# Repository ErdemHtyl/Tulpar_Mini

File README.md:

# MiniTULPAR — Custom Flight Controller Board (FCB)

> A quadcopter flight controller designed from scratch around the STM32F405.
> Schematic, 4-layer PCB, power architecture, sensor integration and firmware
> all live in this repository — no existing open-source flight controller is
> used.

---

## ⚠️ Project Status

This project is **under active development**. The table below shows what is
finished and what is still in progress:

| Component | Status | Notes |
|---|---|---|
| Schematic design | ✅ Rev A complete | `MiniTulpar_Schematic.pdf` |
| PCB layout (4 layer) | ✅ Complete | 53.6 × 53.6 mm, 1.6 mm |
| Manufacturing files (Gerber/BOM/CPL) | ✅ Generated | `mfr/` |
| System architecture documentation | ✅ Complete | `docs/architecture.md` |
| Pin configuration (CubeMX) | ✅ Verified | No timer channel conflicts |
| Clock tree configuration | ✅ Verified | 168 MHz SYSCLK, 48 MHz USB |
| Board fabrication and assembly | 🔄 Planned | — |
| **Firmware** | 🚧 **In development — not started** | See the roadmap below |
| Flight testing | ⏳ Blocked | Depends on firmware |
| Lower-cost board variants | 🔄 Planned | See [Planned Variants](#planned-variants) |

> **Firmware note:** the firmware is **in development**. Nothing described in
> the roadmap below has been implemented yet — drivers, sensor fusion, PID
> control and the safety layer are all still to be written. The architectural
> decisions behind them (bus allocation, timer/DMA assignments, interrupt
> priorities) are documented in advance in `docs/architecture.md`, and
> development will follow that document. **The board does not fly in its
> current state.**

---

## Table of Contents

- [Project Goal](#project-goal)
- [Hardware Overview](#hardware-overview)
- [System Architecture](#system-architecture)
- [Bus Allocation and Rationale](#bus-allocation-and-rationale)
- [Timer and DMA Allocation](#timer-and-dma-allocation)
- [Pin Map](#pin-map)
- [Clock Configuration](#clock-configuration)
- [Firmware Roadmap](#firmware-roadmap)
- [Planned Variants](#planned-variants)
- [Repository Layout](#repository-layout)
- [Development Environment](#development-environment)
- [Known Issues and Rev B Notes](#known-issues-and-rev-b-notes)
- [License](#license)

---

## Project Goal

The goal is to **design, understand and implement every hardware and software
component** rather than buying an off-the-shelf flight controller (Betaflight /
ArduPilot hardware). That includes:

- Multi-layer PCB design and power architecture
- Writing IMU / barometer / magnetometer drivers from scratch
- Sensor fusion (Mahony / Madgwick / EKF)
- PID-based stabilisation and mixing
- Generating the DShot ESC protocol directly from timers and DMA
- GPS, telemetry, blackbox logging and the failsafe/safety layer

Every design decision is recorded in `docs/architecture.md` together with the
alternative that was rejected and the reason it was rejected.

---

## Hardware Overview

| Feature | Value |
|---|---|
| MCU | **STM32F405RGT6** — Cortex-M4F, 168 MHz, 1 MB Flash, 192 KB RAM (128 KB SRAM + 64 KB CCM) |
| Oscillator | 8 MHz HSE (ECS-80-10-30B-CKM-TR) |
| PCB | 4 layer, 53.6 × 53.6 mm, 1.6 mm thickness |
| Power | USB-C 5 V ↔ VIN, Schottky OR (D2/D3) + JP1 jumper → **LD39200PU33R** 3.3 V / 2 A LDO |
| IMU | **ICM-42670-P** (accel + gyro) — SPI1 @ 21 MHz, INT1 → PC4 |
| Barometer | **BMP581** — I2C2, 0x46, INT → PB1 |
| Magnetometer | **IIS2MDC** — I2C2, 0x1E, DRDY → PB2 |
| Blackbox flash | **W25Q128JVS** 16 MB — SPI2 @ 21 MHz |
| Motor outputs | 4× **DShot600** — TIM8_CH1..CH4 (PC6–PC9), single DMA burst |
| Auxiliary PWM | TIM1_CH1/CH3 (PA8/PA10) + TIM3_CH1/CH2 (PB4/PB5 — camera gimbal) |
| RC input | CRSF / ELRS — UART4 (J10) |
| GPS | USART2 (J12) |
| Telemetry | UART5 (J11) |
| Spare UART | USART3 (J5) |
| External I²C | I2C1 (J6) — separate from the internal sensor bus |
| ADC | Battery voltage → PC3 (ADC1_IN13), external → PC2 (ADC1_IN12) |
| USB | USB-C 2.0, USBLC6-2SC6 ESD protection + polyfuse + 5.1 kΩ CC |
| Debug | 10-pin 1.27 mm SWD (J13) |
| LEDs | 3× status LEDs + power LED |

---

## System Architecture

```mermaid
flowchart TB
    subgraph PWR["Power Tree"]
        XT[["VIN / Rail"]]
        USB5[["USB-C 5 V"]]
        OR{{"D2 / D3 Schottky OR<br/>+ JP1"}}
        LDO["U1 LD39200PU33R<br/>3.3 V / 2 A"]
        XT --> OR
        USB5 --> OR
        OR --> LDO
        LDO --> V33[("+3.3 V")]
        LDO -. "FB1 600Ω@100MHz" .-> VDDA[("VDDA")]
    end

    subgraph MCU["STM32F405RGT6 @ 168 MHz"]
        CORE["Cortex-M4F<br/>FPU + DSP"]
    end

    subgraph FAST["High rate — SPI1 @ 21 MHz"]
        IMU["U2 ICM-42670-P<br/>CS = PA4 · INT1 → PC4"]
    end

    subgraph SLOW["Slow sensor bus — I2C2 @ 400 kHz"]
        BARO["U4 BMP581 · 0x46"]
        MAG["U6 IIS2MDC · 0x1E"]
    end

    subgraph LOG["Logging — SPI2 @ 21 MHz"]
        FLASH["U7 W25Q128JVS<br/>16 MB · CS = PB12"]
    end

    subgraph ACT["Actuators"]
        ESC["4× ESC · DShot600<br/>TIM8_CH1..CH4"]
        SERVO["Aux PWM · TIM1 / TIM3"]
    end

    subgraph COMM["Serial links"]
        RC["CRSF/RC · UART4"]
        GPS["GPS · USART2"]
        TLM["Telemetry · UART5"]
        AUX["Spare · USART3"]
        EXTI2C["External I2C1"]
    end

    V33 --> MCU
    IMU <-->|SPI1| CORE
    BARO <-->|I2C2| CORE
    MAG <-->|I2C2| CORE
    FLASH <-->|SPI2| CORE
    CORE --> ESC
    CORE --> SERVO
    RC <--> CORE
    GPS <--> CORE
    TLM <--> CORE
    AUX <--> CORE
    EXTI2C <--> CORE
```

**The critical data path:** the IMU's INT1 line raises an EXTI interrupt → a
SPI1 DMA burst read starts → the DMA completion interrupt runs the filter, PID
and mixer chain → the result is encoded into a DShot frame and handed to the
TIM8 DMA. The whole chain completes **inside one interrupt context**, never
waiting on any other peripheral.

---

## Bus Allocation and Rationale

The founding principle of the architecture:

> **The critical path lives on SPI. Everything non-critical lives on I²C.**

| Device | Bus | Speed | Why |
|---|---|---|---|
| ICM-42670-P | **SPI1** (alone) | 21 MHz | The only high-rate path; the same read takes ~68× longer on I²C |
| BMP581 + IIS2MDC | **I2C2** (shared) | 400 kHz | ~4 % combined bus load; neither is on the critical path |
| W25Q128JVS | **SPI2** (alone) | 21 MHz | A sector erase can take 400 ms and must never delay a gyro read |
| External devices | **I2C1** | 400 kHz | A cable means ESD, capacitance and lockup risk — isolated from the internal sensors |

**Why the IMU is on SPI.** A 15-byte sample read takes ~5.7 µs on SPI1 versus
~388 µs on I²C Fast-mode:

| Loop rate | SPI load | I²C load |
|---|---|---|
| 1 kHz | 0.6 % | 39 % |
| 1.6 kHz | 0.9 % | 62 % |
| 4 kHz | 2.3 % | impossible |

Beyond bandwidth: SPI is deterministic (no clock stretching), has no bus-lockup
failure mode, survives the noisy environment of ESCs switching at 20–40 kHz
thanks to its push-pull drivers, and costs the CPU nothing when paired with DMA.

---

## Timer and DMA Allocation

### Timer assignment

The current CubeMX pin configuration is **conflict-free** — all four motor
outputs, both auxiliary PWM channels and both gimbal channels are usable at the
same time:

| Function | Timer | Channel | Pin | Timer clock |
|---|---|---|---|---|
| Motor 1–4 | **TIM8** | CH1–CH4 | PC6 / PC7 / PC8 / PC9 | 168 MHz (APB2) |
| Aux PWM 1–2 | TIM1 | CH1 / CH3 | PA8 / PA10 | 168 MHz (APB2) |
| Camera gimbal 1–2 | TIM3 | CH2 / CH1 | PB5 / PB4 | 84 MHz (APB1) |

The motors are on **TIM8** rather than TIM3 for four reasons:

1. TIM3_CH1 can be routed to either PC6 or PB4, but only one at a time — putting
   the motors on TIM8 leaves TIM3 entirely free for the gimbal outputs.
2. TIM8 sits on APB2, so its timer clock is 168 MHz (twice TIM3's) — twice the
   DShot bit-timing resolution.
3. TIM8 is an advanced-control timer: its break input can drive a hardware motor
   cutoff for failsafe later.
4. All four motors on one timer are bit-synchronous and need only a single DMA
   burst (TIM8_UP + DMAR).

Because the two gimbal channels sit on TIM3 (84 MHz) and the aux PWM channels on
TIM1 (168 MHz), driving both at a common servo rate means programming the two
timers separately with different prescaler values.

### DShot600 timing (TIM8 @ 168 MHz)

| Protocol | ARR | CCR for "0" | CCR for "1" | Frame |
|---|---|---|---|---|
| DShot300 | 559 | 210 | 420 | 53.3 µs |
| **DShot600** | **279** | **105** | **210** | **26.7 µs** |

DShot is digital: **ESC calibration stops being a step that exists**, and every
frame carries a 4-bit CRC — a command corrupted by noise is discarded by the ESC
instead of silently applying the wrong throttle.

### DMA assignments (under the RM0090 Table 42/43 constraints)

**DMA2**

| Stream | Ch | Assignment |
|---|---|---|
| S0 | 3 | SPI1_RX — IMU read *(the critical path)* |
| S1 | 7 | TIM8_UP — DShot burst output |
| S5 | 3 | SPI1_TX — IMU command |
| S2/S3/S4/S7 | 7 | *Reserved:* bidirectional DShot (unused in v1) |

**DMA1**

| Stream | Ch | Assignment |
|---|---|---|
| S0 | 4 | UART5_RX — telemetry |
| S1 | 4 | USART3_RX — spare |
| S2 | 4 | UART4_RX — CRSF/RC *(420 kbaud, critical)* |
| S3 | 0 | SPI2_RX — flash |
| S4 | 0 | SPI2_TX — blackbox |
| S5 | 4 | USART2_RX — GPS (circular + IDLE) |
| S6 | 4 | USART2_TX — GPS configuration |
| S7 | 4 | UART5_TX — telemetry |

I2C1/I2C2, UART4_TX, USART3_TX and ADC1 are interrupt-driven — their streams
went to higher-value work and their load is negligible.

### Interrupt priorities (NVIC)

| Priority | Interrupt |
|---|---|
| 0 | EXTI4 — IMU INT1 (timestamps the sampling instant) |
| 1 | DMA2_S0 — SPI1_RX complete (triggers the control chain) |
| 2 | DMA2_S1 — TIM8_UP (motor frame) |
| 3 | DMA1_S2 — UART4_RX (RC / failsafe) |
| 4 | DMA1_S5 — USART2_RX (GPS) |
| 5 | I2C2_EV / I2C2_ER |
| 6 | SysTick |
| 7 | Flash, UART5, USB |

> **The rule:** blackbox writes, USB and telemetry must **never** preempt the
> control loop.

### Target timing budget (1 kHz loop)

| Step | Duration | Occupies the CPU? |
|---|---|---|
| IMU SPI burst read | 5.7 µs | No (DMA) |
| Filtering (3× biquad + PT1) | ~10 µs | Yes |
| Attitude update (Mahony) | ~20 µs | Yes |
| PID (3 axes) | ~12 µs | Yes |
| Mixer + motor limiting | ~4 µs | Yes |
| DShot frame encoding | ~6 µs | Yes |
| **Total CPU** | **~52 µs** | **≈ 5 % load** |

---

## Pin Map

This table is the single source of truth for the pin map — it is never
maintained in two places.

| Port | Signal | Function |
|---|---|---|
| PA4 / PA5 / PA6 / PA7 | SPI1 CS/SCK/MISO/MOSI | IMU |
| PC4 | INT_IMU1 | EXTI4 — data ready |
| PB12 / PB13 / PB14 / PB15 | SPI2 CS/SCK/MISO/MOSI | Blackbox flash |
| PB10 / PB11 | I2C2 SCL/SDA | Internal sensor bus |
| PB1 / PB2 | INT_BAR / INT_MAG | EXTI1 / EXTI2 |
| PB8 / PB9 | I2C1 SCL/SDA | External connector (J6) |
| PC6 / PC7 / PC8 / PC9 | DSHOT_1..4 | **TIM8_CH1..CH4** |
| PA8 / PA10 | Aux PWM 1–2 | TIM1_CH1 / TIM1_CH3 |
| PB4 / PB5 | CAM_GIMBAL2 / CAM_GIMBAL1 | TIM3_CH1 / TIM3_CH2 |
| PA0 / PA1 | UART4 TX/RX | CRSF / RC (J10) |
| PA2 / PA3 | USART2 TX/RX | GPS (J12) |
| PC12 / PD2 | UART5 TX/RX | Telemetry (J11) |
| PC10 / PC11 | USART3 TX/RX | Spare (J5) |
| PC2 / PC3 | ADC1_IN12 / ADC1_IN13 | External ADC / battery |
| PA11 / PA12 / PA9 | USB DM/DP/VBUS | USB-C |
| PA13 / PA14 | SWDIO / SWCLK | SWD (J13) |
| PC13 / PC14 / PC15 | LD1 / LD2 / LD3 | Status LEDs |
| PH0 / PH1 | HSE IN/OUT | 8 MHz crystal |

**Unused and available:** PA15, PB0, PB3, PB6, PB7, PC0, PC1, PC5.
PB6/PB7 = USART1, PB0/PB1 = TIM3_CH3/CH4, and PB0 + PC5 together are exactly the
chip select + interrupt pair a second IMU would need.

Full pin table including physical pin numbers: [`docs/architecture.md`](docs/architecture.md)

---

## Clock Configuration

8 MHz HSE crystal → PLL (M = 4, N = 168, P = 2) → **168 MHz SYSCLK**, with the
PLL Q divider set to 7 for the 48 MHz USB clock. CSS (clock security system) is
enabled, so a crystal failure falls back to the HSI instead of stopping the
core.

| Domain | Prescaler | Frequency |
|---|---|---|
| SYSCLK / HCLK (AHB, core, memory, DMA) | /1 | **168 MHz** |
| APB1 peripheral clock (PCLK1) | /4 | 42 MHz |
| APB1 timer clock (TIM3 …) | — | 84 MHz |
| APB2 peripheral clock (PCLK2) | /2 | 84 MHz |
| APB2 timer clock (**TIM1, TIM8**) | — | **168 MHz** |
| USB OTG FS | PLL /Q = 7 | 48 MHz |
| IWDG | LSI | 32 kHz |

The RTC runs from the internal LSI — no LSE crystal is fitted, because PC14/PC15
are used as status LED outputs. This is irrelevant for a flight controller.

SPI1 and SPI2 both run at 21 MHz: SPI1 from PCLK2 (84 MHz ÷ 4) and SPI2 from
PCLK1 (42 MHz ÷ 2), both comfortably under the ICM-42670-P's 24 MHz and the
W25Q128's 133 MHz limits.

---

## Firmware Roadmap

> 🚧 **Nothing in this section has been implemented yet.** The order is chosen to
> minimise bring-up risk; each step depends on the previous one being verified.

### Stage 0 — Bring-up
- [ ] Project skeleton and build system
- [ ] SWD connection and LED blink — is the board alive?
- [ ] Bring up the clock tree on hardware and measure it (8 MHz HSE → 168 MHz)
- [ ] Generate the pin configuration from the pin map above
- [ ] Debug console over USB CDC

### Stage 1 — Sensors
- [ ] SPI1 + DMA driver, ICM-42670-P WHO_AM_I
- [ ] Raw IMU reads (INT1 → EXTI → DMA burst chain)
- [ ] IMU internal UI filter / ODR configuration *(anti-aliasing is critical)*
- [ ] I2C2 as a **non-blocking state machine** + timeouts + bus recovery (9× SCL)
- [ ] BMP581 driver (pressure → altitude)
- [ ] IIS2MDC driver + hard/soft-iron calibration
- [ ] Gyro/accel calibration and temperature compensation

### Stage 2 — Actuators
- [ ] DShot600 frame generation via TIM8 + DMAR burst
- [ ] Motor test mode — **props off**, verify frames on a scope
- [ ] Mixer (quad X), motor limiting / airmode

### Stage 3 — Control
- [ ] Gyro filter chain (biquad LPF + notch + PT1)
- [ ] Attitude estimation — Mahony (EKF later)
- [ ] Rate PID loop (acro mode)
- [ ] Angle/horizon loop (self-level)
- [ ] PID gain tuning interface

### Stage 4 — RC and safety
- [ ] CRSF parser (UART4 DMA + IDLE line)
- [ ] Arming/disarming state machine + sensor health check
- [ ] **IWDG** (~50 ms, fed only by the main control loop)
- [ ] Gyro timeout → immediate disarm
- [ ] RC timeout (~500 ms) → progressive throttle-cut failsafe
- [ ] Battery voltage monitoring + low-voltage warning

### Stage 5 — Navigation and logging
- [ ] GPS UBX/NMEA parser (USART2 DMA)
- [ ] Blackbox logging (SPI2 → W25Q128, pre-erase while idle)
- [ ] Telemetry (UART5) and the CRSF back-channel
- [ ] Altitude hold → position hold → return-to-home

### Stage 6 — Advanced
- [ ] Bidirectional DShot (RPM telemetry) + RPM-based notch filtering
- [ ] EKF-based sensor fusion
- [ ] Host-side unit tests (HIL/SIL)

**The safety layer is non-negotiable:** motors are **always** disarmed at
power-up; arming requires low throttle plus an explicit arm command plus a
sensor health check.

---

## Planned Variants

MiniTULPAR Rev A is the reference design — it is deliberately built with
good parts rather than cheap ones, so that when something misbehaves the cause
is the design and not the bill of materials.

**More affordable versions of this board will be added later.** The plan is to
publish lower-cost variants alongside the reference design, so the project stays
buildable on a smaller budget:

- Cheaper sensor options (a lower-cost IMU and barometer in place of the
  ICM-42670-P / BMP581)
- A reduced-feature build — dropping the blackbox flash, the magnetometer or the
  gimbal outputs where they are not needed
- Widely stocked, low-cost alternatives for the passives, connectors and the
  regulator
- Where a substitution changes the firmware, the difference will be documented
  rather than hidden behind a build flag

Each variant will ship with its own BOM and a short note on what was traded
away. The reference design stays the one that is documented and tested first.

---

## Repository Layout

Hardware and firmware live in a **single repository** (monorepo) — when a pin
changes, KiCad, the documentation and the firmware are all updated in the same
commit.

```
custom-fcb/
├── README.md
├── docs/                    architecture, power tree, pinout, BOM, test plan
│   ├── architecture.md      design decisions and their rationale (EN)
│   └── images/
├── hardware/
│   ├── MiniTULPAR.kicad_pro / .kicad_sch / .kicad_pcb
│   ├── libs/                custom symbol + footprint libraries
│   ├── datasheets/
│   └── production/          Gerber / drill / BOM / CPL — gitignored
└── firmware/                🚧 in development — nothing implemented yet
    ├── drivers/             imu, baro, mag, gps, crsf, esc/dshot
    ├── fusion/              mahony / madgwick / ekf
    ├── control/             pid, rate and angle loops, mixer
    ├── telemetry/
    ├── safety/              failsafe, arming, watchdog
    └── tests/               host-side unit tests
```

**Version control rules**

- `hardware/production/` is gitignored. Gerbers are added by hand only when a
  board is ordered, together with `git tag hw-vX.Y` — so it is always certain
  which board was built from which files.
- Flight logs (`logs/`, `*.bbl`) never enter the repository.
- `.gitattributes` normalises line endings to LF in the repository.

---

## Development Environment

**Hardware side**

| Tool | Version / note |
|---|---|
| KiCad | 8.x |
| Schematic | `MiniTULPAR.kicad_sch` (+ `scheme_diagram.kicad_sch`) |
| Custom footprints | `ftp.pretty/` |
| Custom symbols | `MiniTULPAR_sym.kicad_sym` |

**Firmware side** *(planned)*

| Tool | Note |
|---|---|
| Toolchain | `arm-none-eabi-gcc` |
| Build | CMake + Ninja |
| Peripheral layer | STM32CubeF4 (mostly LL; register level on the critical path) |
| Pin & clock configuration | STM32CubeMX |
| Debug | ST-Link / J-Link + OpenOCD, SWO trace |
| Measurement | Loop-time profiling with the DWT cycle counter |

**Ordering a board**

```powershell
git tag -a hw-v0.1 -m "First board order"
git push --tags
gh release create hw-v0.1 hardware\production\*.zip
```

---

## Known Issues and Rev B Notes

Findings from the schematic review. **None of them makes the board
non-functional**, but they should be decided before fabrication.

| # | Issue | Status / recommendation |
|---|---|---|
| 1 | **ICM-42670-P ODR ceiling of 1.6 kHz** — this is the low-power member of the family, not the ICM-42688-P. An 8 kHz loop is **not possible** on this board (sensor-limited, not bus-limited). | Target a **1 kHz PID loop**. Because of the aliasing risk, the internal UI filter must be configured deliberately and the IMU soft-mounted. |
| 2 | **The battery divider is off-board**, with no overvoltage protection. | Rev B: 1 kΩ series into PC3 plus a Schottky clamp to 3.3 V. |
| 3 | **LDO thermal budget** — 0.85 W at 500 mA with 5 V in. J5/J6/J7/J10/J11/J12 all supply 3.3 V, and a GPS module alone can draw 100–150 mA. | Thermal via array under the LDO; the load budget belongs in `docs/power-tree.md`. |
| 4 | **DShot pins after reset** are high-impedance. | Confirm the ESCs do not apply throttle in that state; add pull-downs on the motor lines if they do (Rev B). |

---

## License

**BSD 3-Clause License** — Copyright © 2026 Erdem Hatayoğlu.

One licence covers the whole repository: firmware, hardware design files and
documentation. It is permissive — you may use, modify and redistribute this
work in source and binary form, including commercially and in closed-source
products, provided that:

- the copyright notice, the list of conditions and the disclaimer are retained
- neither the project name nor the author's name is used to endorse or promote
  derived products without prior written permission

The work comes with no warranty of any kind. Full text: [`LICENSE`](LICENSE)

New files should carry an SPDX header so each file's licence is unambiguous:

```
SPDX-License-Identifier: BSD-3-Clause
SPDX-FileCopyrightText: 2026 Erdem Hatayoğlu
```

Third-party files (vendor headers, generated peripheral libraries, imported
footprints) keep the licence of their original author; where such a file carries
its own licence header, that header takes precedence.

---

## Disclaimer

This board and its firmware are **in development and untested**. Spinning
propellers can cause serious injury. Always run motor tests **with the
propellers removed**, perform the first closed-loop attempts on a safe test
bench, and verify the arming and failsafe logic before flying. Use this project
entirely at your own risk.

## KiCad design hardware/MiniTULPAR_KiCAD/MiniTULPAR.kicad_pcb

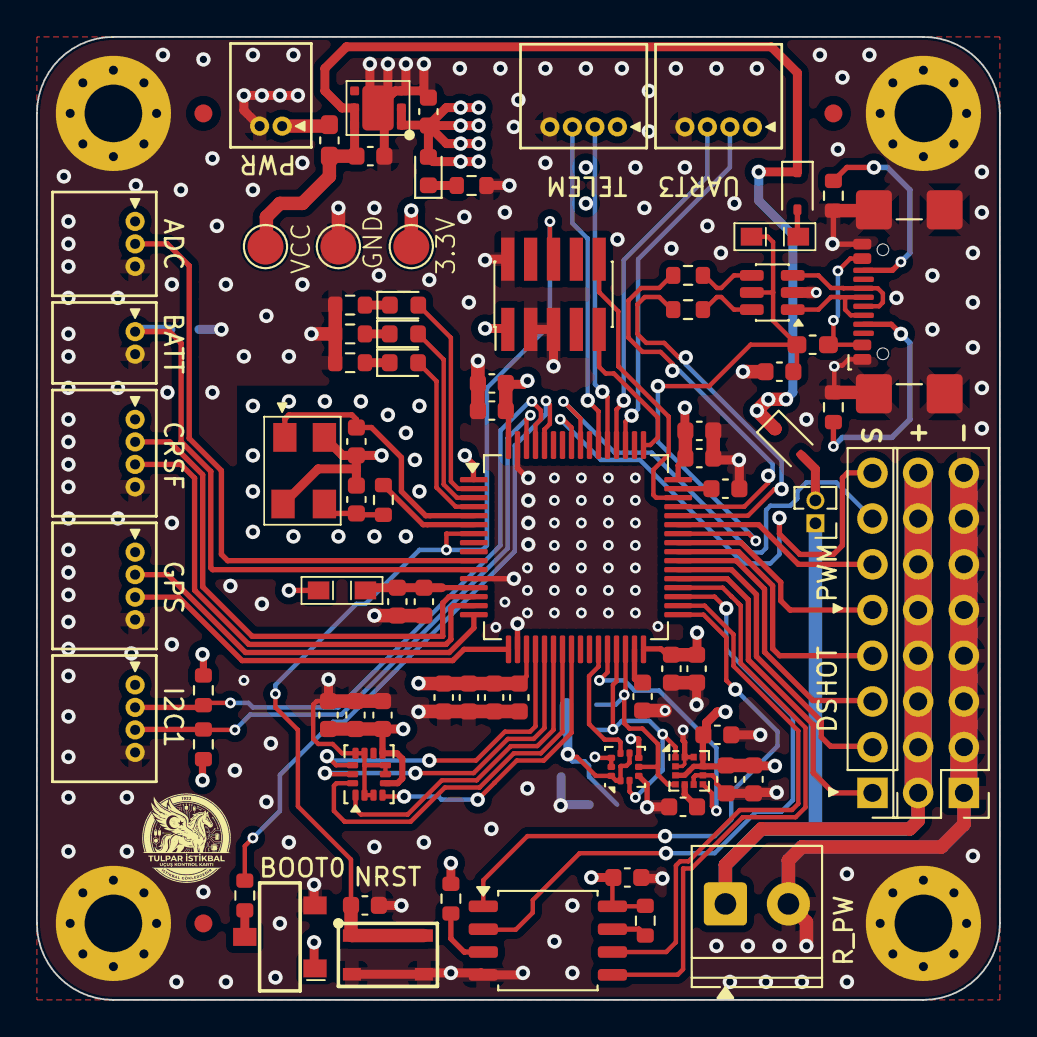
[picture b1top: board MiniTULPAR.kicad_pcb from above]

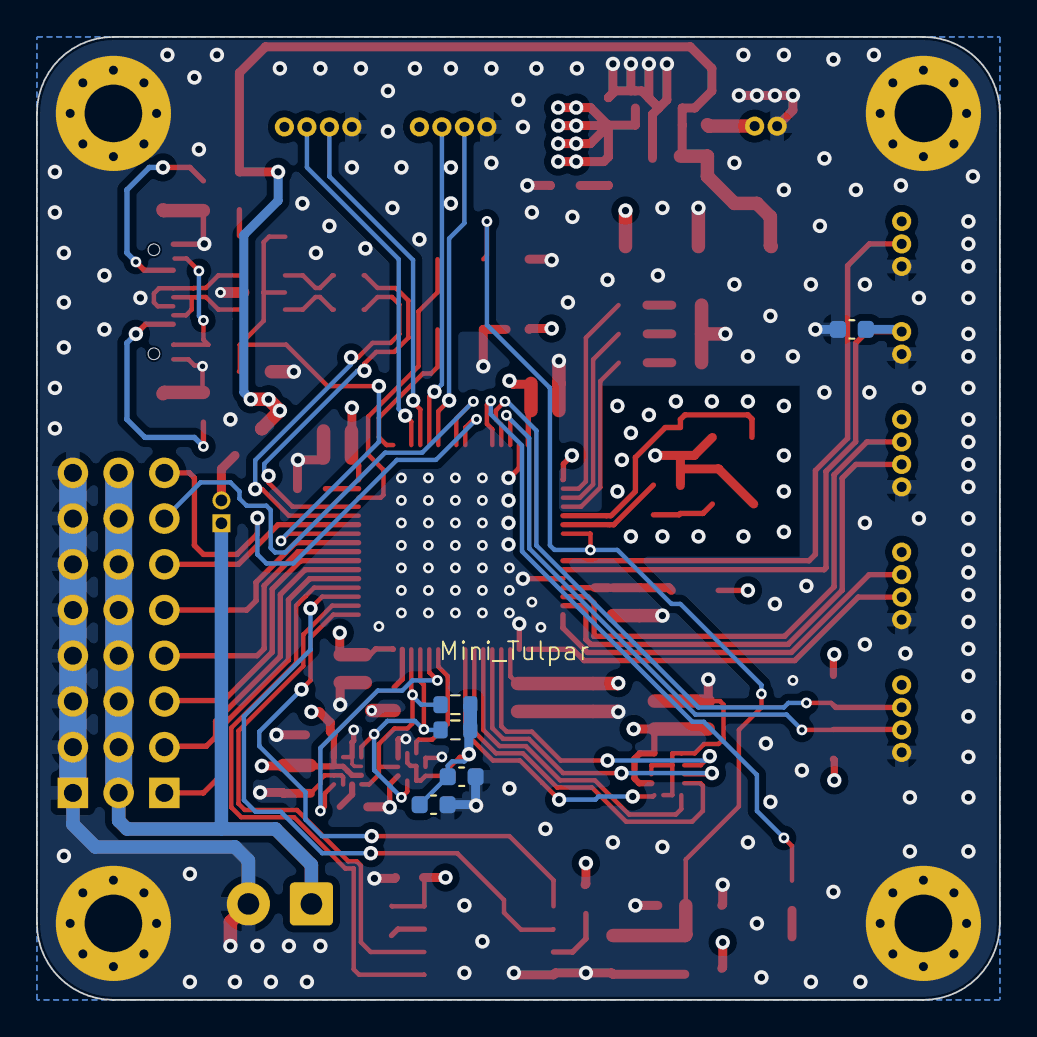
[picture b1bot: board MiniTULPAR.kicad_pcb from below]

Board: 4 copper layers, 53.5 x 53.5 mm, 91 parts (5 on the bottom side), 71 nets.

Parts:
C1, C11, C12, C25: 10uF; C_0603_1608Metric
C2, C3, C4, C5, C6, C7, C8, C9, C10, C15, C18, C22, C23, C24, C26, C27, C29, C30, C31: 0.1uF; C_0603_1608Metric
C13, C14, C19: 10pF; C_0603_1608Metric
C16: 1uF; C_0603_1608Metric
C17, C20, C21: 2.2uF; C_0603_1608Metric
C28: 220nF; C_0603_1608Metric
D1: PWR1_GR; LED_0603_1608Metric
D2, D3: D_Schottky; D_SOD-323
D4: LED_GR; LED_0603_1608Metric
D5: LED_RD; LED_0603_1608Metric
D6: LED_YE; LED_0603_1608Metric
F1, F2: Polyfuse; Fuse_0603_1608Metric_Pad1.05x0.95mm_HandSolder
FB1, FB2: 600 Ohms @ 100 MHz; MPZ2012S601AT000
FID2, FID4, FID5: Fiducial; Fiducial_1mm_Mask2mm
H1: M1; MountingHole_3.2mm_M3_Pad_Via
H3: M2; MountingHole_3.2mm_M3_Pad_Via
H5: M3; MountingHole_3.2mm_M3_Pad_Via
H8: M4; MountingHole_3.2mm_M3_Pad_Via
J1: Rail_Terminal; TerminalBlock_Phoenix_PT-1,5-2-3.5-H_1x02_P3.50mm_Horizontal
J2: Rail_PWR; PinHeader_2x08_P2.54mm_Vertical
J3: Signal; PinHeader_1x08_P2.54mm_Vertical
J4: USB_C_Receptacle_USB2.0_16P; USB_C
J5: UART3; CONN04_530480410_MOL
J6: I2C1; CONN04_530480410_MOL
J7: ADC; CONN03_530480310_MOL
J8: ADC_B; CONN02_530480210_MOL
J9: VIN; CONN02_530480210_MOL
J10: CRSF; CONN04_530480410_MOL
J11: TELEM; CONN04_530480410_MOL
J12: GPS; CONN04_530480410_MOL
J13: SWD; PinHeader_2x05_P1.27mm_Vertical_SMD
JP1: Device_Jumper_NO_Small; PinHeader_1x02_P1.27mm_Vertical
R1: 0; R_0603_1608Metric
R2, R11, R12, R13: 1K; R_0603_1608Metric
R3, R4, R5, R6: 4.7K; R_0603_1608Metric
R7, R8: 5.1K; R_0603_1608Metric
R9, R10: 22; R_0603_1608Metric
R14, R15, R16: 10K; R_0603_1608Metric
S1: PTS815SJM250SMTRLFS
S2: TDD01H0SB1R
TP1: 3.3V_Test; TestPoint_Pad_D2.0mm
TP2: GND_Test; TestPoint_Pad_D2.0mm
TP3: VCC_Test; TestPoint_Pad_D2.0mm
U1: LD39200PU33R
U2: ICM-42670-P; LGA-14_3x2.5mm_P0.5mm_LayoutBorder3x4y
U3: STM32F405RGTx; LQFP-64_10x10mm_P0.5mm
U4: BMP581; ST_HLGA-10_2x2mm_P0.5mm_LayoutBorder3x2y
U5: USBLC6-2SC6; SOT-23-6
U6: IIS2MDC; LGA-12_2x2mm_P0.5mm
U7: W25Q128JVS; SOIC-8_5.3x5.3mm_P1.27mm
X1: 8MHz; ECS-80-10-30B-CKM-TR

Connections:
+3.3V: C1.1, C2.1, C3.1, C4.1, C5.1, C6.1, C7.1, C8.1, C9.1, C10.1, C12.1, C17.1, C18.1, C19.1, C22.1, C23.1, C25.1, C26.1, C27.1, C30.1, D1.2 (A), FB1.1, J5.1, J6.1, J7.1, J10.1, J11.1, J12.1, J13.1, R3.2, R4.2, R5.2, R6.2, R14.1, R16.2, S2.1, TP1.1 (1_1), U1.1 (OUT), U1.2 (SENSE), U2.5 (VDDIO), U2.8 (VDD), U3.1 (VBAT), U3.19 (VDD), U3.32 (VDD), U3.48 (VDD), U3.64 (VDD), U4.1 (VDDIO), U4.6 (CS), U4.10 (VDD), U6.3 (CS), U6.9 (VDD), U6.10 (VDDIO), U7.8 (VCC)
/Scheme Diagram/D+: J4.A6 (D+), J4.B6 (D+), U5.3 (I/O2)
/Scheme Diagram/D-: J4.A7 (D-), J4.B7 (D-), U5.1 (I/O1)
/Scheme Diagram/Rail_PWR: J1.1, J2.2, J2.4, J2.6, J2.8, J2.10, J2.12, J2.14, J2.16, JP1.1
/Scheme Diagram/USB+: R10.2, U5.4 (I/O2)
/Scheme Diagram/USB-: R9.1, U5.6 (I/O1)
/Scheme Diagram/VCAP1: C20.1, U3.31 (VCAP_1)
/Scheme Diagram/VCAP2: C21.1, U3.47 (VCAP_2)
ADC1: J7.2, U3.10 (PC2)
BOOT0: R15.1, U3.60 (BOOT0)
Battery_Voltage: C29.1, J8.1, U3.11 (PC3)
DSHOT_1: J3.1, U3.37 (PC6)
DSHOT_2: J3.2, U3.38 (PC7)
DSHOT_3: J3.3, U3.39 (PC8)
DSHOT_4: J3.4, U3.40 (PC9)
GND: C1.2, C2.2, C3.2, C4.2, C5.2, C6.2, C7.2, C8.2, C9.2, C10.2, C11.2, C12.2, C13.2, C14.2, C15.2, C16.2, C17.2, C18.2, C19.2, C20.2, C21.2, C22.2, C23.2, C24.2, C25.2, C26.2, C27.2, C28.2, C29.2, C30.2, C31.2, H1.1 (1_1), H3.1 (1_1), H5.1 (1_1), H8.1 (1_1), J1.2, J2.1, J2.3, J2.5, J2.7, J2.9, J2.11, J2.13, J2.15, J4.A1 (GND), J4.A12 (GND), J4.B1 (GND), J4.B12 (GND), J4.SH (SHIELD), J5.4, J6.4, J7.3, J8.2, J9.2, J10.4, J11.4, J12.4, J13.2, J13.3, J13.5, R2.2, R7.2, R8.2, R11.2, R12.2, R13.2, S1.3, S1.4, S2.2, TP2.1 (1_1), U1.3 (GND), U1.7 (GND), U2.2 (RESV), U2.3 (RESV), U2.6 (GND), U2.7 (FSYNC), U2.10 (RESV), U2.11 (RESV), U3.12 (VSSA), U3.18 (VSS), U3.63 (VSS), U4.3 (GND), U4.5 (SA0), U4.8 (GND), U4.9 (GND), U5.2 (GND), U6.2 (NC), U6.6 (GND), U6.8 (GND), U6.11 (NC), U6.12 (NC), U7.4 (GND), X1.2 (G), X1.4 (G)
HSE_IN: C13.1, U3.5 (PH0), X1.1
HSE_OUT: R1.2, U3.6 (PH1)
I2C1_SCL: J6.2, R6.1, U3.61 (PB8)
I2C1_SDA: J6.3, R5.1, U3.62 (PB9)
I2C2_SCL: R4.1, U3.29 (PB10), U4.2 (SCL), U6.1 (SCL)
I2C2_SDA: R3.1, U3.30 (PB11), U4.4 (SDA), U6.4 (SDA)
INT_BAR: U3.27 (PB1), U4.7 (INT)
INT_IMU1: U2.4 (INT1), U3.24 (PC4)
INT_MAG: U3.28 (PB2), U6.7 (DRDY)
LD1: D4.2 (A), U3.2 (PC13)
LD2: D5.2 (A), U3.3 (PC14)
LD3: D6.2 (A), U3.4 (PC15)
NRST: C31.1, J13.6, S1.1, S1.2, U3.7 (NRST)
unnamed: C14.1, R1.1, X1.3
unnamed: D1.1 (K), R2.1
unnamed: D2.2 (A), JP1.2
unnamed: D3.2 (A), FB2.2
unnamed: D4.1 (K), R11.1
unnamed: D5.1 (K), R12.1
unnamed: D6.1 (K), R13.1
unnamed: F2.1, J4.A4 (VBUS), J4.A9 (VBUS), J4.B4 (VBUS), J4.B9 (VBUS)
unnamed: J4.A5 (CC1), R7.1
unnamed: J4.B5 (CC2), R8.1
unnamed: F1.2, J9.1
unnamed: R15.2, S2.3 (C)
unnamed: C28.1, U6.5 (C1)
unnamed: R14.2, U7.7 (~HOLD/~RESET/IO_{3})
unnamed: R16.1, U7.3 (~WP/IO_{2})
PWM_1: J3.5, U3.41 (PA8)
PWM_2: J3.6, U3.43 (PA10)
PWM_3: J3.7, U3.56 (PB4)
PWM_4: J3.8, U3.57 (PB5)
SPI1_CS1: U2.12 (AP_CS), U3.20 (PA4)
SPI1_MISO: U2.1 (AP_SDO), U3.22 (PA6)
SPI1_MOSI: U2.14 (AP_SDI), U3.23 (PA7)
SPI1_SCK: U2.13 (AP_SCLK), U3.21 (PA5)
SPI2_CS: U3.33 (PB12), U7.1 (~CS)
SPI2_MISO: U3.35 (PB14), U7.2 (DO/IO_{1})
SPI2_MOSI: U3.36 (PB15), U7.5 (DI/IO_{0})
SPI2_SCK: U3.34 (PB13), U7.6 (CLK)
SWCLK: J13.9, U3.49 (PA14)
SWDIO: J13.10, U3.46 (PA13)
UART4_RX: J10.3, U3.15 (PA1)
UART4_TX: J10.2, U3.14 (PA0)
UART5_RX: J11.3, U3.54 (PD2)
UART5_TX: J11.2, U3.53 (PC12)
USART2_RX: J12.3, U3.17 (PA3)
USART2_TX: J12.2, U3.16 (PA2)
USART3_RX: J5.3, U3.52 (PC11)
USART3_TX: J5.2, U3.51 (PC10)
USB_N: R9.2, U3.44 (PA11)
USB_P: R10.1, U3.45 (PA12)
USB_VBUS: C24.1, F2.2, FB2.1, U3.42 (PA9), U5.5 (VBUS)
VCC: C11.1, D2.1 (K), D3.1 (K), F1.1, TP3.1 (1_1), U1.5 (EN), U1.6 (IN)
VDDA: C15.1, C16.1, FB1.2, U3.13 (VDDA)
